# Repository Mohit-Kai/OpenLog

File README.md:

## SURE-TRUST-PROJECTS-G4-PCB- OpenLog

OpenLog is a compact serial data logger built around the ATmega328 microcontroller. It automatically records incoming serial data to a microSD card, supporting baud rates up to 115200 bps. Configuration is handled through a simple text file stored on the card. This makes OpenLog an effective solution for sensor data logging, system monitoring, and remote debugging applications.

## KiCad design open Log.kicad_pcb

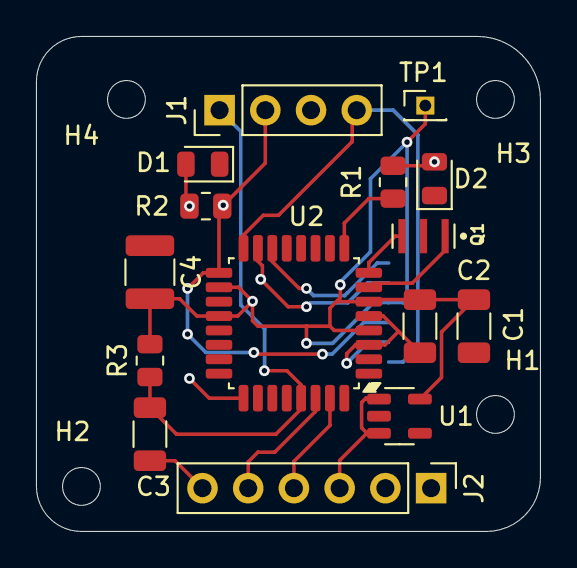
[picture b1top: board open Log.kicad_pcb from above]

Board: 2 copper layers, 28.0 x 27.5 mm, 20 parts (1 on the bottom side), 15 nets.

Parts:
C1: 10uF; C_1206_3216Metric
C2, C3: 0.1uF; C_1206_3216Metric
C4: 0.1uF; C_1210_3225Metric
D1: GREEN; LED_0805_2012Metric
D2: BLUE; LED_0805_2012Metric
H1, H2, H3, H4: MountingHole; MountingHole_2.1mm
J1: PinHeader_1x04_P2.54mm_Vertical
J2: Conn_01x06_Pin; PinHeader_1x06_P2.54mm_Vertical
J3: Micro_SD_Card; microSD_HC_Hirose_DM3AT-SF-PEJM5
Q1: 16MHZ; RESONATOR 16MHZ
R1: 330; R_0805_2012Metric
R2, R3: 1K; R_0805_2012Metric
TP1: PinHeader_1x01_P1.27mm_Vertical
U1: 3.3V MIC5205; SOT-23-5
U2: ATmega328P-A; TQFP-32_7x7mm_P0.8mm

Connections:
3.3V: C1.1, C2.1, C4.2, J3.4 (VCC), R3.1, TP1.1, U1.5 (OUT), U2.4 (VCC), U2.6 (VCC), U2.18 (AVCC), U2.20 (AREF)
CS: J3.2 (CS), U2.14 (PB2(SS/OC1B))
DTR: C3.1, J2.6
GND: C1.2, C2.2, C4.1, D1.1 (K), D2.1 (K), J2.1, J2.2, J3.6 (GND), J3.9, Q1.2, U1.2 (GND), U2.3 (GND), U2.5 (GND), U2.21 (AGND)
MISO: J1.4, J3.7 (DO), U2.16 (PB4(MISO))
MOSI: J1.3, J3.3 (DI), U2.15 (PB3(MOSI/OC2))
unnamed: D1.2 (A), D2.2 (A), R1.2, R2.2
unnamed: Q1.1, U2.7 (PB6/XTAL1)
unnamed: Q1.3, U2.8 (PB7/XTAL2)
unnamed: R1.1, U2.9 (PD5(T1))
RAW: J2.3, U1.1 (IN), U1.3 (EN)
RST: C3.2, J1.1, R3.2, U2.29 (PC6/~RESET)
RXI: J2.5, U2.30 (PD0(RDX))
SCK: J1.2, J3.5 (SCK), R2.1, U2.17 (PB5(SCK))
TXO: J2.4, U2.31 (PD1(TXD))

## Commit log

2025-09-19 Update README.md
    OpenLog is a compact serial data logger built around the ATmega328 microcontroller. It automatically records incoming serial data to a microSD card, supporting baud rates up to 115200 bps. Configurat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
2025-09-19 Open Log
